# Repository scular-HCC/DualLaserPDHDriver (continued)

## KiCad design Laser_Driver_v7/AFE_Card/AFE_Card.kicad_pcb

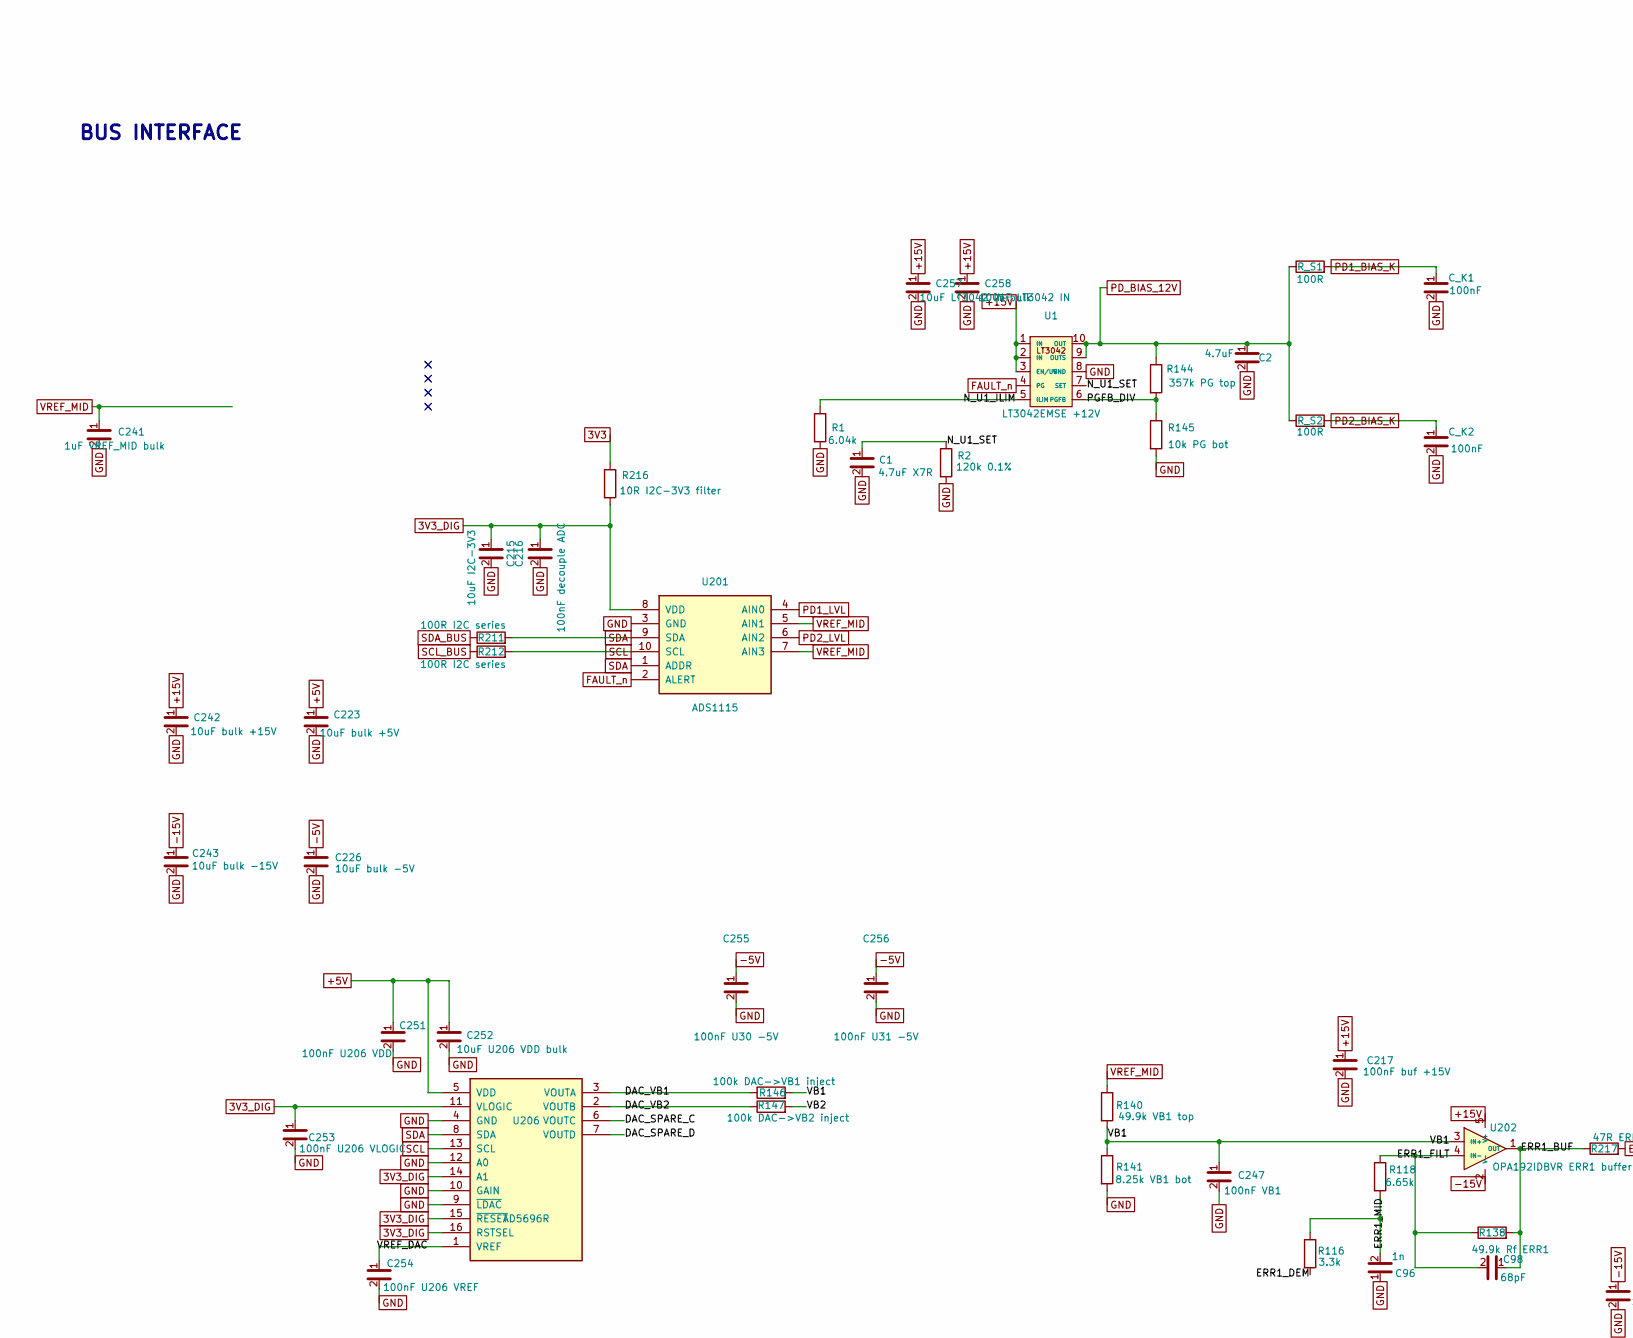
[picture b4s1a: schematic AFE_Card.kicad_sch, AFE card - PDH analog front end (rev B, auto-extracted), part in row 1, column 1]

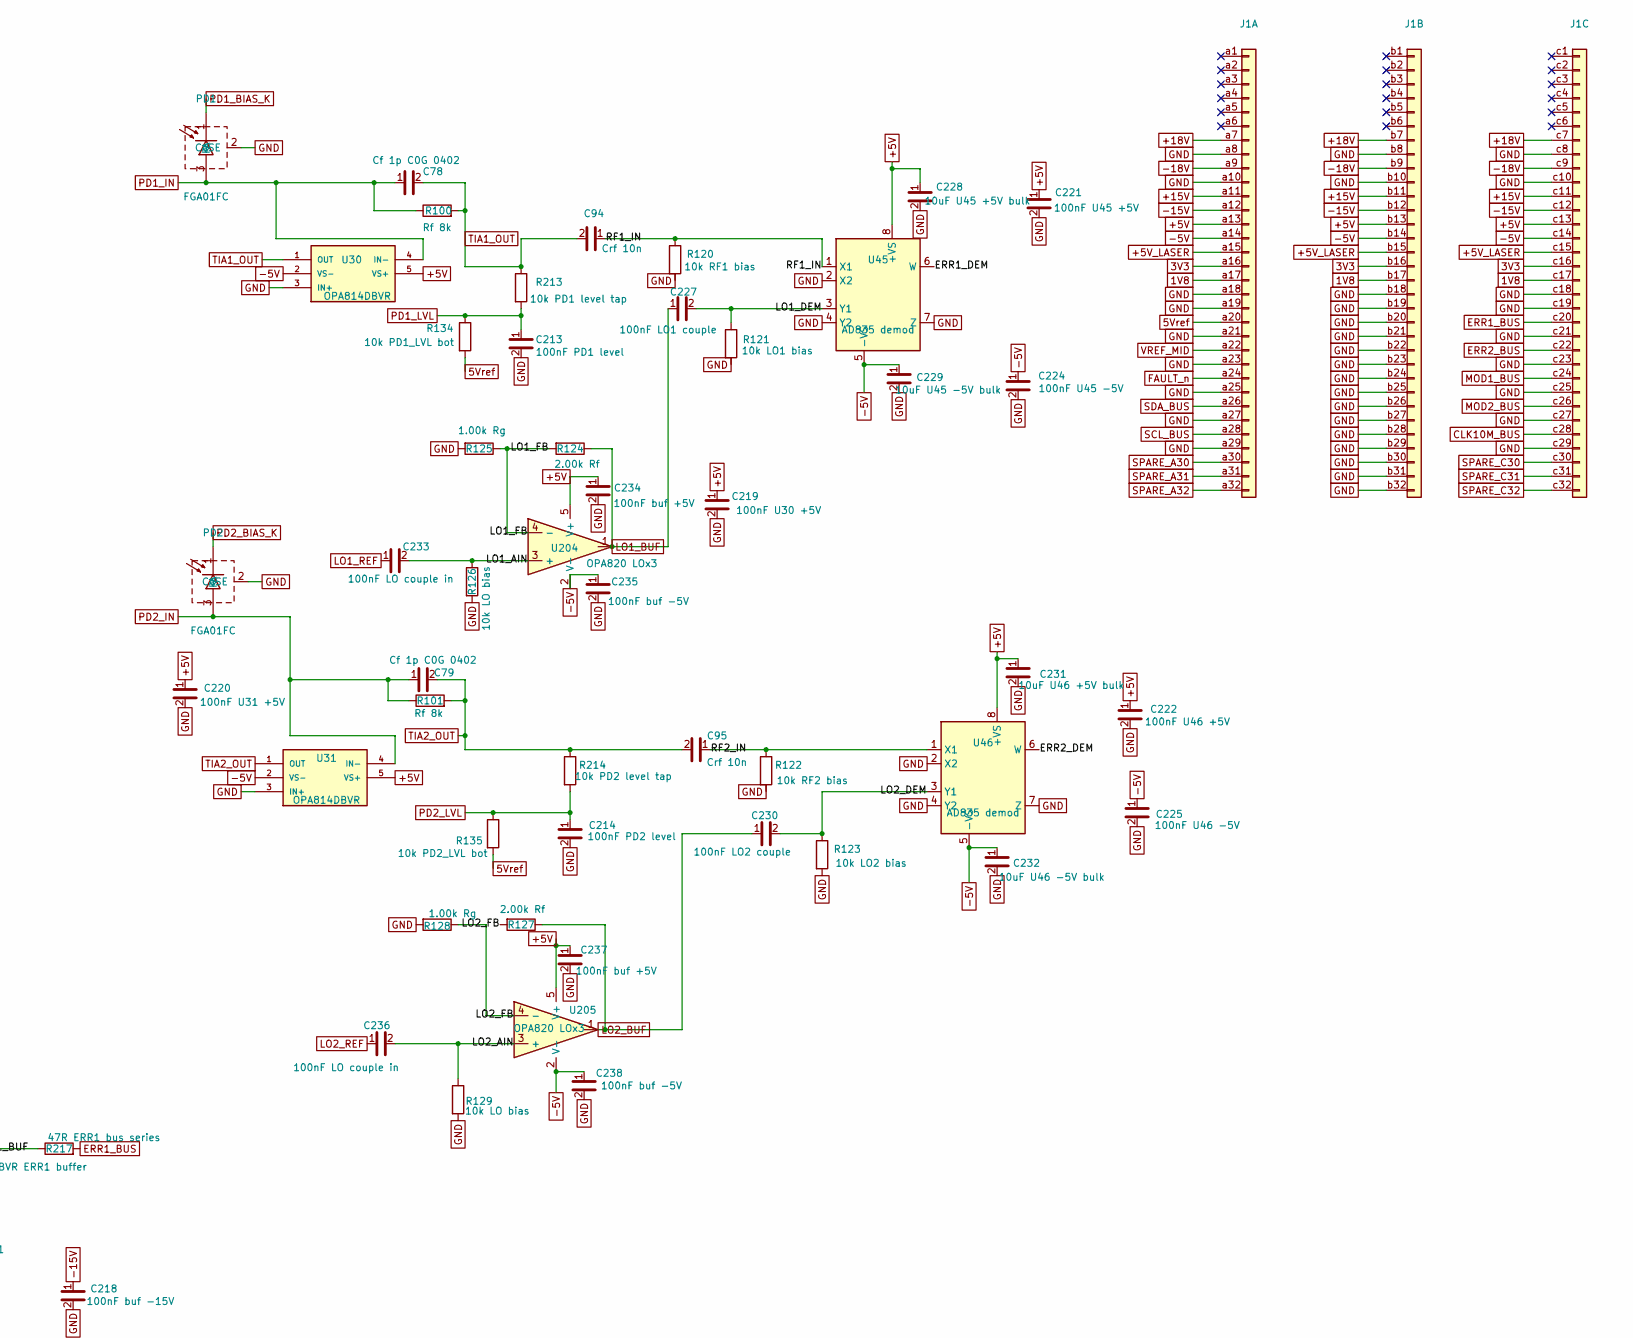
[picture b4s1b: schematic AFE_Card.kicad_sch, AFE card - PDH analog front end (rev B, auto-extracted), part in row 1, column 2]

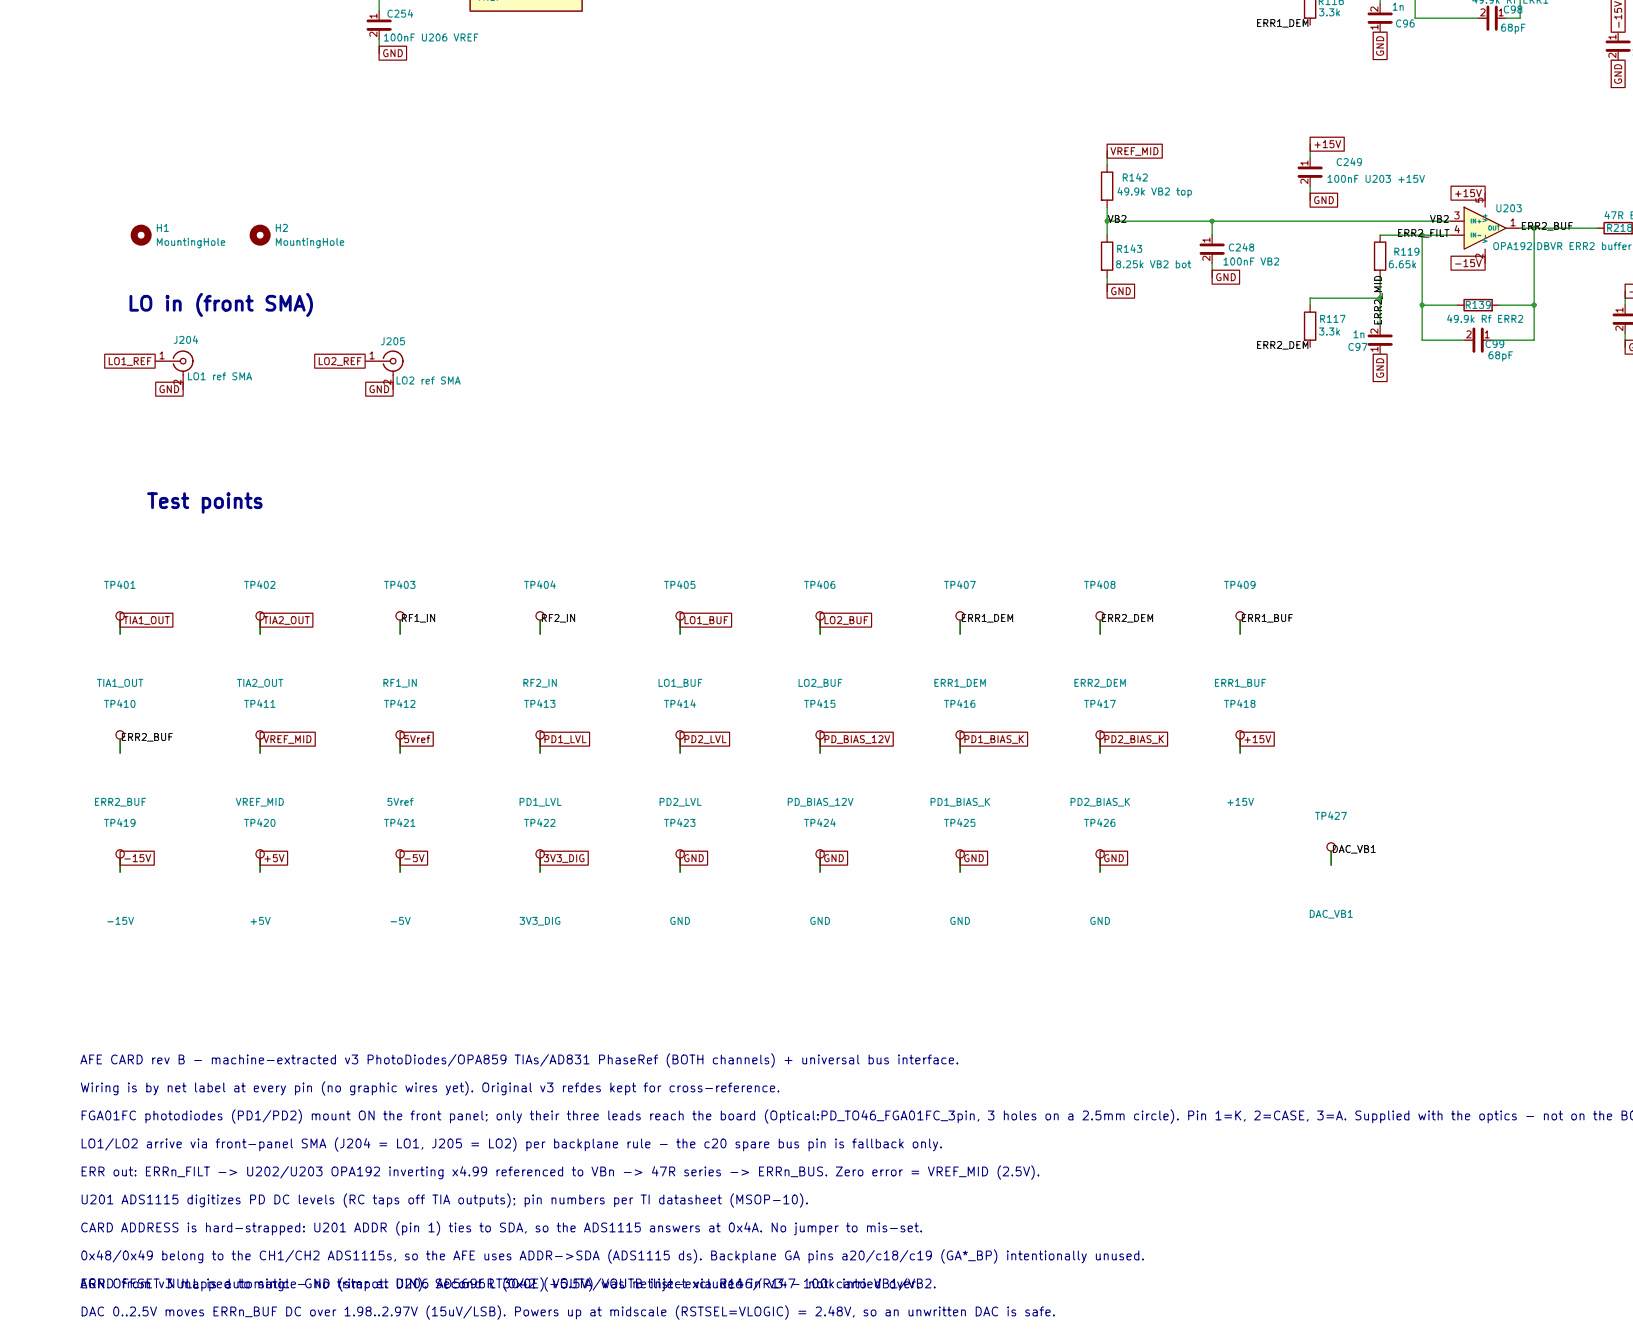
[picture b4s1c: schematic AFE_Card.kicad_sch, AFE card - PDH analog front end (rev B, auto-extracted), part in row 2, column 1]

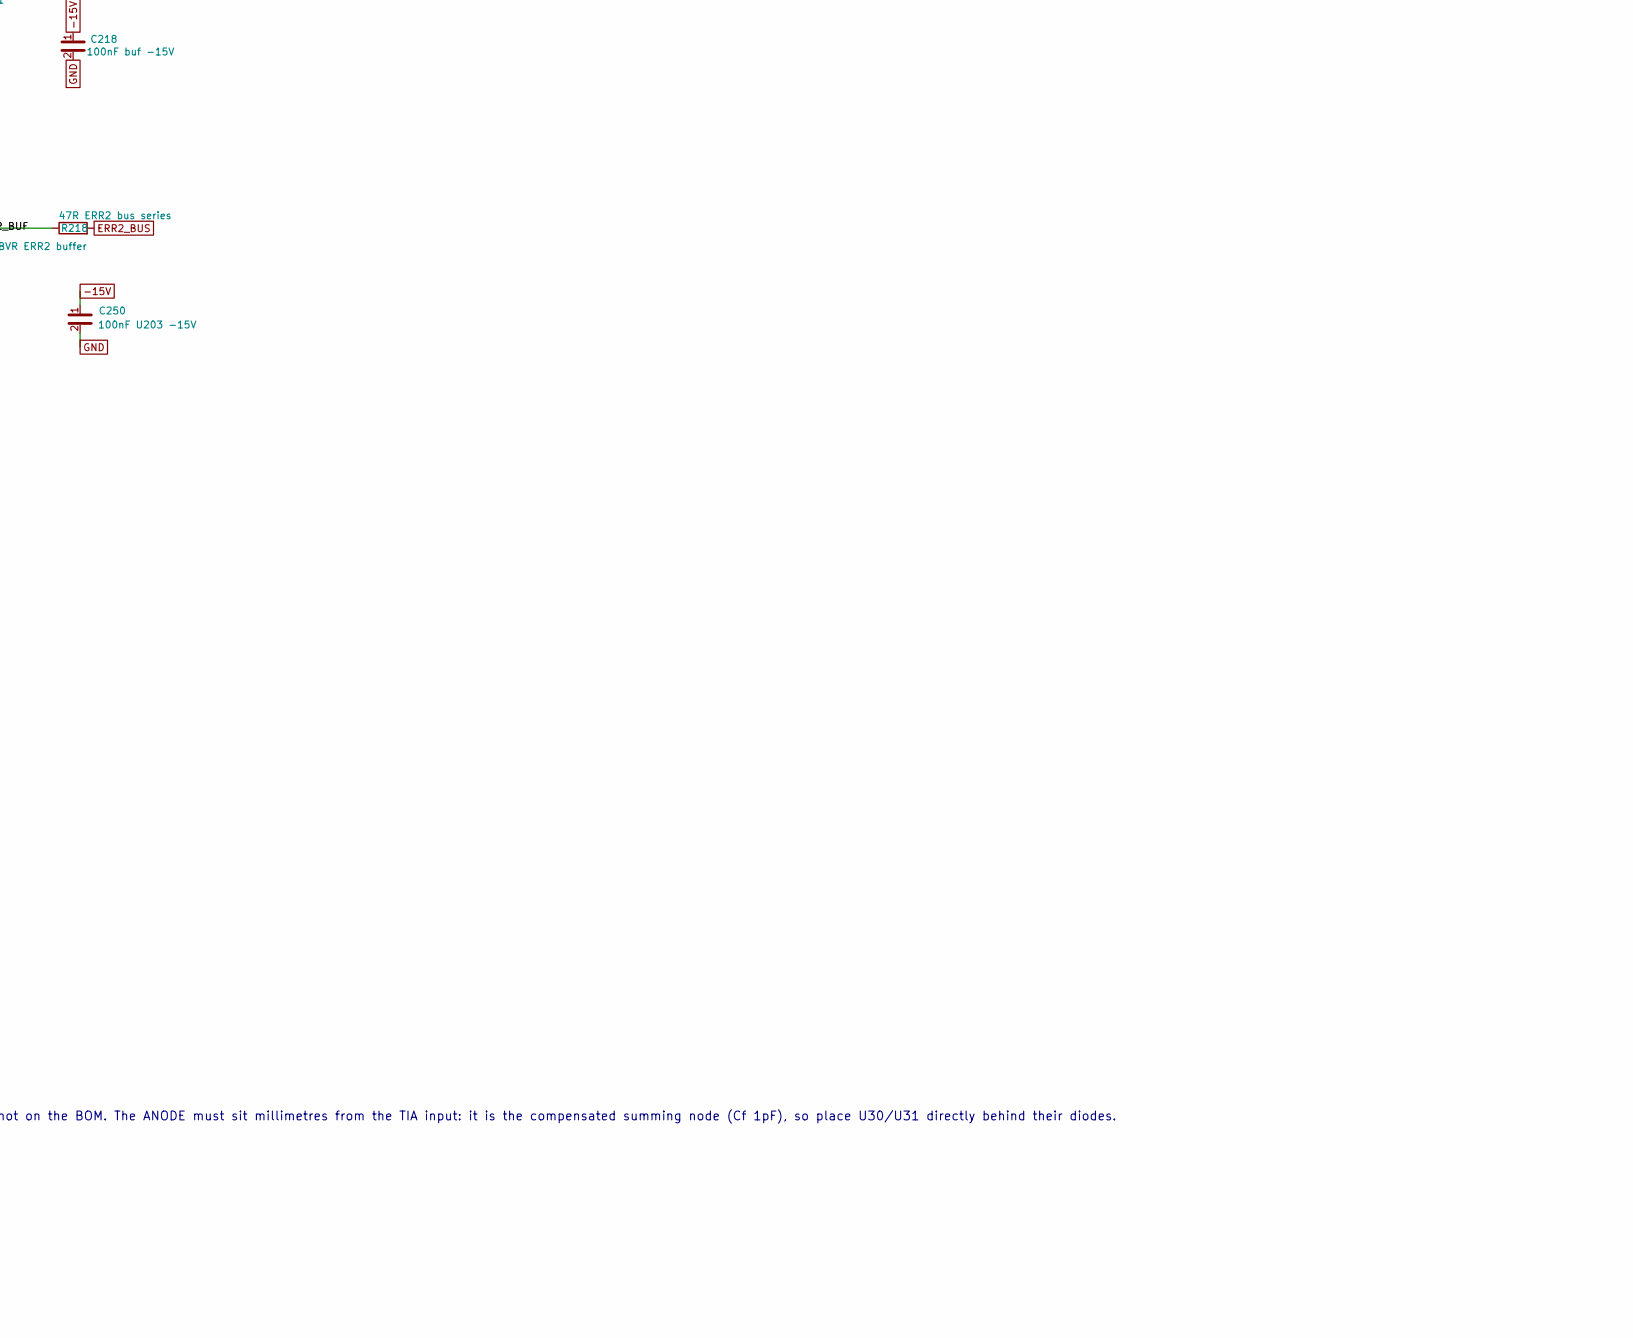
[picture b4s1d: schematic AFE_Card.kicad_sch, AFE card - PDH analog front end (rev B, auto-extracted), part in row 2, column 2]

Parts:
C1: 4.7uF X7R; C_0805_2012Metric_Pad1.18x1.45mm_HandSolder
C2: 4.7uF; C_0805_2012Metric_Pad1.18x1.45mm_HandSolder
C78, C79: Cf 1p C0G 0402; C_0402_1005Metric_Pad0.74x0.62mm_HandSolder
C94, C95: Crf 10n; C_0805_2012Metric_Pad1.18x1.45mm_HandSolder
C96, C97: 1n; C_0805_2012Metric_Pad1.18x1.45mm_HandSolder
C98, C99: 68pF; C_0805_2012Metric_Pad1.18x1.45mm_HandSolder
C213: 100nF PD1 level; C_0805_2012Metric_Pad1.18x1.45mm_HandSolder
C214: 100nF PD2 level; C_0805_2012Metric_Pad1.18x1.45mm_HandSolder
C215: 10uF I2C-3V3; C_0805_2012Metric_Pad1.18x1.45mm_HandSolder
C216: 100nF decouple ADC; C_0805_2012Metric_Pad1.18x1.45mm_HandSolder
C217: 100nF buf +15V; C_0805_2012Metric_Pad1.18x1.45mm_HandSolder
C218: 100nF buf -15V; C_0805_2012Metric_Pad1.18x1.45mm_HandSolder
C219: 100nF U30 +5V; C_0805_2012Metric_Pad1.18x1.45mm_HandSolder
C220: 100nF U31 +5V; C_0805_2012Metric_Pad1.18x1.45mm_HandSolder
C221: 100nF U45 +5V; C_0805_2012Metric_Pad1.18x1.45mm_HandSolder
C222: 100nF U46 +5V; C_0805_2012Metric_Pad1.18x1.45mm_HandSolder
C223: 10uF bulk +5V; C_0805_2012Metric_Pad1.18x1.45mm_HandSolder
C224: 100nF U45 -5V; C_0805_2012Metric_Pad1.18x1.45mm_HandSolder
C225: 100nF U46 -5V; C_0805_2012Metric_Pad1.18x1.45mm_HandSolder
C226: 10uF bulk -5V; C_0805_2012Metric_Pad1.18x1.45mm_HandSolder
C227: 100nF LO1 couple; C_0805_2012Metric_Pad1.18x1.45mm_HandSolder
C228: 10uF U45 +5V bulk; C_0805_2012Metric_Pad1.18x1.45mm_HandSolder
C229: 10uF U45 -5V bulk; C_0805_2012Metric_Pad1.18x1.45mm_HandSolder
C230: 100nF LO2 couple; C_0805_2012Metric_Pad1.18x1.45mm_HandSolder
C231: 10uF U46 +5V bulk; C_0805_2012Metric_Pad1.18x1.45mm_HandSolder
C232: 10uF U46 -5V bulk; C_0805_2012Metric_Pad1.18x1.45mm_HandSolder
C233, C236: 100nF LO couple in; C_0805_2012Metric_Pad1.18x1.45mm_HandSolder
C234, C237: 100nF buf +5V; C_0805_2012Metric_Pad1.18x1.45mm_HandSolder
C235, C238: 100nF buf -5V; C_0805_2012Metric_Pad1.18x1.45mm_HandSolder
C241: 1uF VREF_MID bulk; C_0805_2012Metric_Pad1.18x1.45mm_HandSolder
C242: 10uF bulk +15V; C_0805_2012Metric_Pad1.18x1.45mm_HandSolder
C243: 10uF bulk -15V; C_0805_2012Metric_Pad1.18x1.45mm_HandSolder
C247: 100nF VB1; C_0805_2012Metric_Pad1.18x1.45mm_HandSolder
C248: 100nF VB2; C_0805_2012Metric_Pad1.18x1.45mm_HandSolder
C249: 100nF U203 +15V; C_0805_2012Metric_Pad1.18x1.45mm_HandSolder
C250: 100nF U203 -15V; C_0805_2012Metric_Pad1.18x1.45mm_HandSolder
C251: 100nF U206 VDD; C_0805_2012Metric_Pad1.18x1.45mm_HandSolder
C252: 10uF U206 VDD bulk; C_0805_2012Metric_Pad1.18x1.45mm_HandSolder
C253: 100nF U206 VLOGIC; C_0805_2012Metric_Pad1.18x1.45mm_HandSolder
C254: 100nF U206 VREF; C_0805_2012Metric_Pad1.18x1.45mm_HandSolder
C255: 100nF U30 -5V; C_0805_2012Metric_Pad1.18x1.45mm_HandSolder
C256: 100nF U31 -5V; C_0805_2012Metric_Pad1.18x1.45mm_HandSolder
C257: 10uF LT3042 IN bulk; C_0805_2012Metric_Pad1.18x1.45mm_HandSolder
C258: 100nF LT3042 IN; C_0805_2012Metric_Pad1.18x1.45mm_HandSolder
C_K1, C_K2: 100nF; C_0805_2012Metric_Pad1.18x1.45mm_HandSolder
H1, H2: MountingHole; MountingHole_2.7mm
J1: DIN41612_03x32_C_Split; DIN41612_C_3x32_Male_Horizontal_THT
J204: LO1 ref SMA; SMA_Amphenol_132203-12_Horizontal
J205: LO2 ref SMA; SMA_Amphenol_132203-12_Horizontal
PD1, PD2: FGA01FC; PD_FGA01FC_EdgeBracket
R1: 6.04k; R_0805_2012Metric_Pad1.20x1.40mm_HandSolder
R2: 120k 0.1%; R_0805_2012Metric_Pad1.20x1.40mm_HandSolder
R100, R101: Rf 8k; R_0805_2012Metric_Pad1.20x1.40mm_HandSolder
R116, R117: 3.3k; R_0805_2012Metric_Pad1.20x1.40mm_HandSolder
R118, R119: 6.65k; R_0805_2012Metric_Pad1.20x1.40mm_HandSolder
R120: 10k RF1 bias; R_0805_2012Metric_Pad1.20x1.40mm_HandSolder
R121: 10k LO1 bias; R_0805_2012Metric_Pad1.20x1.40mm_HandSolder
R122: 10k RF2 bias; R_0805_2012Metric_Pad1.20x1.40mm_HandSolder
R123: 10k LO2 bias; R_0805_2012Metric_Pad1.20x1.40mm_HandSolder
R124, R127: 2.00k Rf; R_0805_2012Metric_Pad1.20x1.40mm_HandSolder
R125, R128: 1.00k Rg; R_0805_2012Metric_Pad1.20x1.40mm_HandSolder
R126, R129: 10k LO bias; R_0805_2012Metric_Pad1.20x1.40mm_HandSolder
R134: 10k PD1_LVL bot; R_0805_2012Metric_Pad1.20x1.40mm_HandSolder
R135: 10k PD2_LVL bot; R_0805_2012Metric_Pad1.20x1.40mm_HandSolder
R138: 49.9k Rf ERR1; R_0805_2012Metric_Pad1.20x1.40mm_HandSolder
R139: 49.9k Rf ERR2; R_0805_2012Metric_Pad1.20x1.40mm_HandSolder
R140: 49.9k VB1 top; R_0805_2012Metric_Pad1.20x1.40mm_HandSolder
R141: 8.25k VB1 bot; R_0805_2012Metric_Pad1.20x1.40mm_HandSolder
R142: 49.9k VB2 top; R_0805_2012Metric_Pad1.20x1.40mm_HandSolder
R143: 8.25k VB2 bot; R_0805_2012Metric_Pad1.20x1.40mm_HandSolder
R144: 357k PG top; R_0805_2012Metric_Pad1.20x1.40mm_HandSolder
R145: 10k PG bot; R_0805_2012Metric_Pad1.20x1.40mm_HandSolder
R146: 100k DAC->VB1 inject; R_0805_2012Metric_Pad1.20x1.40mm_HandSolder
R147: 100k DAC->VB2 inject; R_0805_2012Metric_Pad1.20x1.40mm_HandSolder
R211, R212: 100R I2C series; R_0805_2012Metric_Pad1.20x1.40mm_HandSolder
R213: 10k PD1 level tap; R_0805_2012Metric_Pad1.20x1.40mm_HandSolder
R214: 10k PD2 level tap; R_0805_2012Metric_Pad1.20x1.40mm_HandSolder
R216: 10R I2C-3V3 filter; R_0805_2012Metric_Pad1.20x1.40mm_HandSolder
R217: 47R ERR1 bus series; R_0805_2012Metric_Pad1.20x1.40mm_HandSolder
R218: 47R ERR2 bus series; R_0805_2012Metric_Pad1.20x1.40mm_HandSolder
R_S1, R_S2: 100R; R_0805_2012Metric_Pad1.20x1.40mm_HandSolder
TP401: TIA1_OUT; TestPoint_Pad_D1.0mm
TP402: TIA2_OUT; TestPoint_Pad_D1.0mm
TP403: RF1_IN; TestPoint_Pad_D1.0mm
TP404: RF2_IN; TestPoint_Pad_D1.0mm
TP405: LO1_BUF; TestPoint_Pad_D1.0mm
TP406: LO2_BUF; TestPoint_Pad_D1.0mm
TP407: ERR1_DEM; TestPoint_Pad_D1.0mm
TP408: ERR2_DEM; TestPoint_Pad_D1.0mm
TP409: ERR1_BUF; TestPoint_Pad_D1.0mm
TP410: ERR2_BUF; TestPoint_Pad_D1.0mm
TP411: VREF_MID; TestPoint_Pad_D1.0mm
TP412: 5Vref; TestPoint_Pad_D1.0mm
TP413: PD1_LVL; TestPoint_Pad_D1.0mm
TP414: PD2_LVL; TestPoint_Pad_D1.0mm
TP415: PD_BIAS_12V; TestPoint_Pad_D1.0mm
TP416: PD1_BIAS_K; TestPoint_Pad_D1.0mm
TP417: PD2_BIAS_K; TestPoint_Pad_D1.0mm
TP418: +15V; TestPoint_Pad_D1.0mm
TP419: -15V; TestPoint_Pad_D1.0mm
TP420: +5V; TestPoint_Pad_D1.0mm
TP421: -5V; TestPoint_Pad_D1.0mm
TP422: 3V3_DIG; TestPoint_Pad_D1.0mm
TP423, TP424, TP425, TP426: GND; TestPoint_THTPad_D1.5mm_Drill0.7mm
TP427: DAC_VB1; TestPoint_Pad_D1.0mm
U1: LT3042EMSE +12V; MSOP-10-1EP_3x3mm_P0.5mm_EP1.68x1.88mm
U30, U31: OPA814DBVR; MOUSER_PART_NUMBER 595-OPA814DBVR
U45, U46: AD835 demod; SOIC-8_3.9x4.9mm_P1.27mm
U201: ADS1115; MSOP-10_3x3mm_P0.5mm
U202: OPA192IDBVR ERR1 buffer; SOT-23-5
U203: OPA192IDBVR ERR2 buffer; SOT-23-5
U204, U205: OPA820 LOx3; SOT-23-5
U206: AD5696R; TSSOP-16_4.4x5mm_P0.65mm

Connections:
1V8: J1.a17, J1.b17, J1.c17
3V3: J1.a16, J1.b16, J1.c16, R216.1
3V3_DIG: C215.1, C216.1, C253.1, R216.2, TP422.1 (1_1), U201.8 (VDD), U206.11 (VLOGIC), U206.14 (A1), U206.15 (~RESET), U206.16 (RSTSEL)
5Vref: J1.a20, R134.2, R135.2, TP412.1 (1_1)
+5V: C219.1, C220.1, C221.1, C222.1, C223.1, C228.1, C231.1, C234.1, C237.1, C251.1, C252.1, J1.a13, J1.b13, J1.c13, TP420.1 (1_1), U30.5 (VS+), U31.5 (VS+), U45.8 (+VS), U46.8 (+VS), U204.5 (V+), U205.5 (V+), U206.5 (VDD)
+5V_LASER: J1.a15, J1.b15, J1.c15
+15V: C217.1, C242.1, C249.1, C257.1, C258.1, J1.a11, J1.b11, J1.c11, TP418.1 (1_1), U1.1 (IN), U1.2 (IN), U1.3 (EN/UV), U202.5 (V+), U203.5 (V+)
+18V: J1.a7, J1.b7, J1.c7
-5V: C224.1, C225.1, C226.1, C229.1, C232.1, C235.1, C238.1, C255.1, C256.1, J1.a14, J1.b14, J1.c14, TP421.1 (1_1), U30.2 (VS-), U31.2 (VS-), U45.5 (-VS), U46.5 (-VS), U204.2 (V-), U205.2 (V-)
-15V: C218.1, C243.1, C250.1, J1.a12, J1.b12, J1.c12, TP419.1 (1_1), U202.2 (V-), U203.2 (V-)
-18V: J1.a9, J1.b9, J1.c9
/DAC_SPARE_C: U206.6 (VOUTC)
/DAC_SPARE_D: U206.7 (VOUTD)
/DAC_VB1: R146.1, TP427.1 (1_1), U206.3 (VOUTA)
/DAC_VB2: R147.1, U206.2 (VOUTB)
/ERR1_BUF: C98.1, R138.2, R217.1, TP409.1 (1_1), U202.1 (OUT)
/ERR1_DEM: R116.2, TP407.1 (1_1), U45.6 (W)
/ERR1_FILT: C98.2, R118.1, R138.1, U202.4 (IN-)
/ERR1_MID: C96.2, R116.1, R118.2
/ERR2_BUF: C99.1, R139.2, R218.1, TP410.1 (1_1), U203.1 (OUT)
/ERR2_DEM: R117.2, TP408.1 (1_1), U46.6 (W)
/ERR2_FILT: C99.2, R119.1, R139.1, U203.4 (IN-)
/ERR2_MID: C97.2, R117.1, R119.2
/LO1_AIN: C233.2, R126.1, U204.3 (+)
/LO1_DEM: C227.2, R121.1, U45.3 (Y1)
/LO1_FB: R124.2, R125.1, U204.4 (-)
/LO2_AIN: C236.2, R129.1, U205.3 (+)
/LO2_DEM: C230.2, R123.1, U46.3 (Y1)
/LO2_FB: R127.2, R128.1, U205.4 (-)
/N_U1_ILIM: R1.1, U1.5 (ILIM)
/N_U1_SET: C1.1, R2.1, U1.7 (SET)
/PGFB_DIV: R144.2, R145.1, U1.6 (PGFB)
/RF1_IN: C94.1, R120.1, TP403.1 (1_1), U45.1 (X1)
/RF2_IN: C95.1, R122.1, TP404.1 (1_1), U46.1 (X1)
/VB1: C247.1, R140.2, R141.1, R146.2, U202.3 (IN+)
/VB2: C248.1, R142.2, R143.1, R147.2, U203.3 (IN+)
/VREF_DAC: C254.1, U206.1 (VREF)
CLK10M_BUS: J1.c28
ERR1_BUS: J1.c20, R217.2
ERR2_BUS: J1.c22, R218.2
FAULT_n: J1.a24, U1.4 (PG), U201.2 (ALERT)
GND: C1.2, C2.2, C96.1, C97.1, C213.2, C214.2, C215.2, C216.2, C217.2, C218.2, C219.2, C220.2, C221.2, C222.2, C223.2, C224.2, C225.2, C226.2, C228.2, C229.2, C231.2, C232.2, C234.2, C235.2, C237.2, C238.2, C241.2, C242.2, C243.2, C247.2, C248.2, C249.2, C250.2, C251.2, C252.2, C253.2, C254.2, C255.2, C256.2, C257.2, C258.2, C_K1.2, C_K2.2, J1.a8, J1.a10, J1.a18, J1.a19, J1.a21, J1.a23, J1.a25, J1.a27, J1.a29, J1.b8, J1.b10, J1.b18, J1.b19, J1.b20, J1.b21, J1.b22, J1.b23, J1.b24, J1.b25, J1.b26, J1.b27, J1.b28, J1.b29, J1.b30, J1.b31, J1.b32, J1.c8, J1.c10, J1.c18, J1.c19, J1.c21, J1.c23, J1.c25, J1.c27, J1.c29, J204.2 (Ext), J205.2 (Ext), PD1.2 (CASE), PD2.2 (CASE), R1.2, R2.2, R120.2, R121.2, R122.2, R123.2, R125.2, R126.2, R128.2, R129.2, R141.2, R143.2, R145.2, TP423.1 (1_1), TP424.1 (1_1), TP425.1 (1_1), TP426.1 (1_1), U1.8 (GND), U1.11 (Pad), U30.3 (IN+), U31.3 (IN+), U45.2 (X2), U45.4 (Y2), U45.7 (Z), U46.2 (X2), U46.4 (Y2), U46.7 (Z), U201.3 (GND), U206.4 (GND), U206.9 (~LDAC), U206.10 (GAIN), U206.12 (A0)
LO1_BUF: C227.1, R124.1, TP405.1 (1_1), U204.1
LO1_REF: C233.1, J204.1 (In)
LO2_BUF: C230.1, R127.1, TP406.1 (1_1), U205.1
LO2_REF: C236.1, J205.1 (In)
MOD1_BUS: J1.c24
MOD2_BUS: J1.c26
PD1_BIAS_K: C_K1.1, PD1.1 (K), R_S1.2, TP416.1 (1_1)
PD1_IN: C78.1, PD1.3 (A), R100.1, U30.4 (IN-)
PD1_LVL: C213.1, R134.1, R213.2, TP413.1 (1_1), U201.4 (AIN0)
PD2_BIAS_K: C_K2.1, PD2.1 (K), R_S2.2, TP417.1 (1_1)
PD2_IN: C79.1, PD2.3 (A), R101.1, U31.4 (IN-)
PD2_LVL: C214.1, R135.1, R214.2, TP414.1 (1_1), U201.6 (AIN2)
PD_BIAS_12V: C2.1, R144.1, R_S1.1, R_S2.1, TP415.1 (1_1), U1.9 (OUTS), U1.10 (OUT)
SCL: R212.2, U201.10 (SCL), U206.13 (SCL)
SCL_BUS: J1.a28, R212.1
SDA: R211.2, U201.1 (ADDR), U201.9 (SDA), U206.8 (SDA)
SDA_BUS: J1.a26, R211.1
SPARE_A30: J1.a30
SPARE_A31: J1.a31
SPARE_A32: J1.a32
SPARE_C30: J1.c30
SPARE_C31: J1.c31
SPARE_C32: J1.c32
TIA1_OUT: C78.2, C94.2, R100.2, R213.1, TP401.1 (1_1), U30.1 (OUT)
TIA2_OUT: C79.2, C95.2, R101.2, R214.1, TP402.1 (1_1), U31.1 (OUT)
VREF_MID: C241.1, J1.a22, R140.1, R142.1, TP411.1 (1_1), U201.5 (AIN1), U201.7 (AIN3)

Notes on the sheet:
AFE CARD rev B - machine-extracted v3 PhotoDiodes/OPA859 TIAs/AD831 PhaseRef (BOTH channels) + universal bus interface.
U201 ADS1115 digitizes PD DC levels (RC taps off TIA outputs); pin numbers per TI datasheet (MSOP-10).
LO in (front SMA)
CARD ADDRESS is hard-strapped: U201 ADDR (pin 1) ties to SDA, so the ADS1115 answers at 0x4A. No jumper to mis-set.
LO1/LO2 arrive via front-panel SMA (J204 = LO1, J205 = LO2) per backplane rule - the c20 spare bus pin is fallback only.
Test points
BUS INTERFACE
Wiring is by net label at every pin (no graphic wires yet). Original v3 refdes kept for cross-reference.
DAC 0..2.5V moves ERRn_BUF DC over 1.98..2.97V (15uV/LSB). Powers up at midscale (RSTSEL=VLOGIC) = 2.48V, so an unwritten DAC is safe.
AGND from v3 mapped to single GND (star at DIN). Second LT3042 (+5.5V) was netlist-excluded in v3 - not carried over.
FGA01FC photodiodes (PD1/PD2) mount ON the front panel; only their three leads reach the board (Optical:PD_TO46_FGA01FC_3pin, 3 holes on a 2.5mm circle). Pin 1=K, 2=CASE, 3=A. Supplied with the optics - not on the BOM. The ANODE must sit millimetres from the TIA input: it is the compensated summing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
ERR out: ERRn_FILT -> U202/U203 OPA192 inverting x4.99 referenced to VBn -> 47R series -> ERRn_BUS. Zero error = VREF_MID (2.5V).
ERR OFFSET NULL is automatic - no trimpot. U206 AD5696R (0x0E) VOUTA/VOUTB inject via R146/R147 100k into VB1/VB2.
0x48/0x49 belong to the CH1/CH2 ADS1115s, so the AFE uses ADDR->SDA (ADS1115 ds). Backplane GA pins a20/c18/c19 (GA*_BP) intentionally unused.

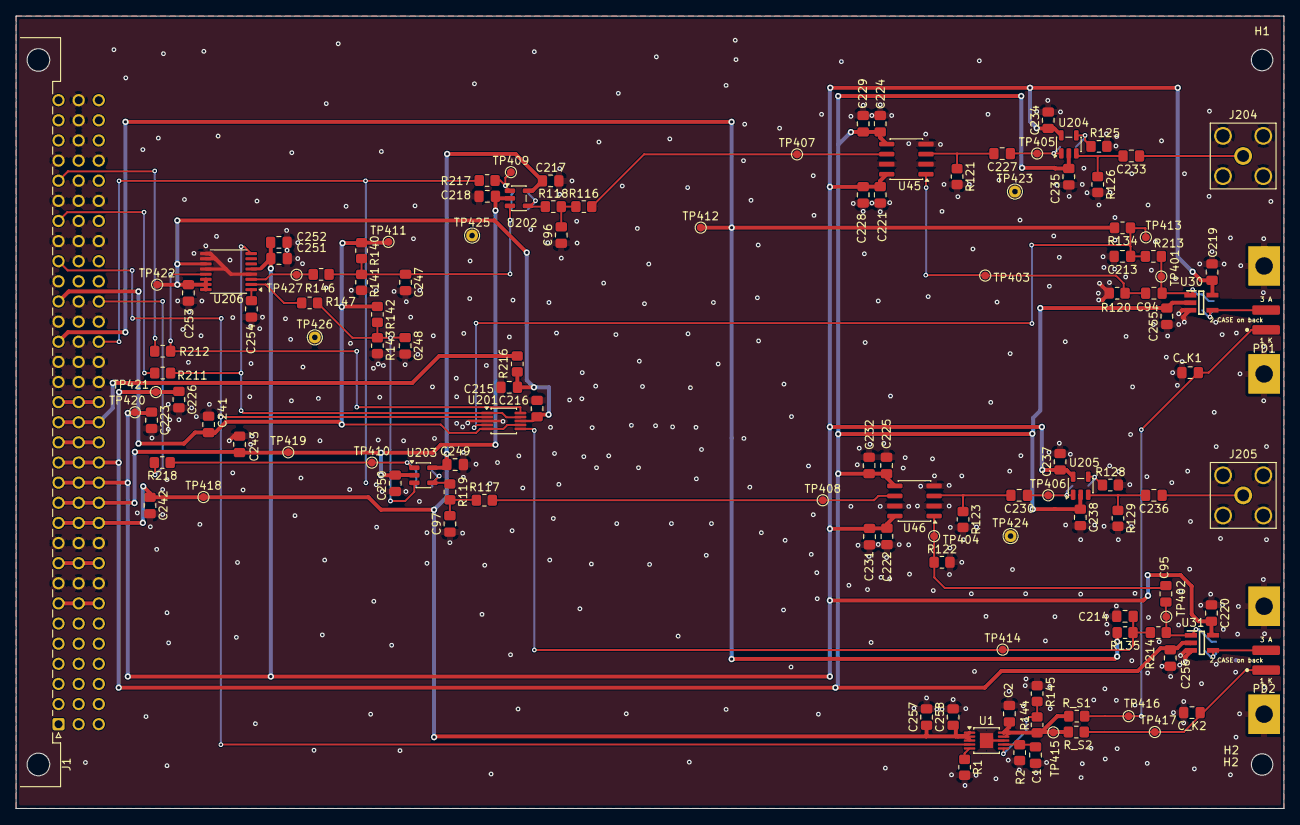
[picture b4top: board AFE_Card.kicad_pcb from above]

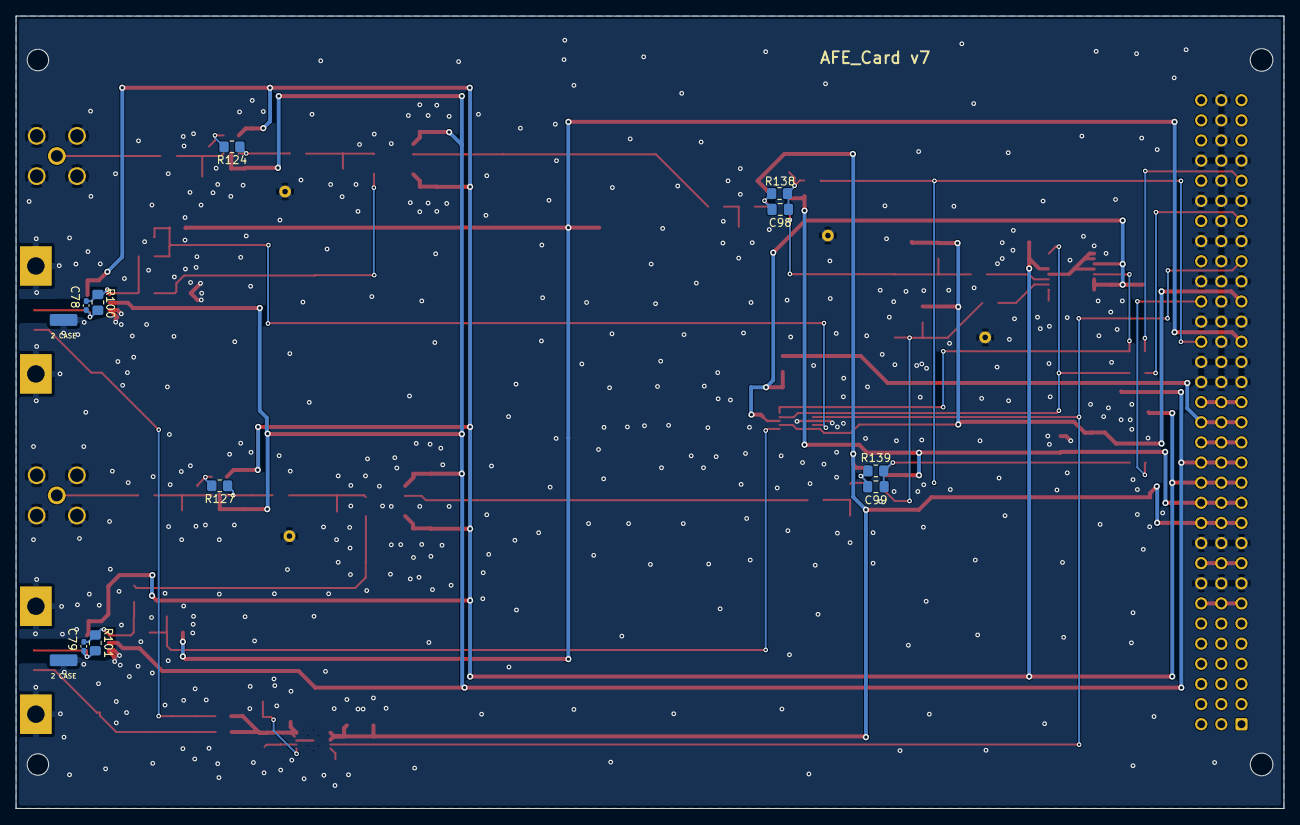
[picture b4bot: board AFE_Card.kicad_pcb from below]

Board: 2 copper layers, 160.0 x 100.0 mm, 137 parts (10 on the bottom side), 57 nets.

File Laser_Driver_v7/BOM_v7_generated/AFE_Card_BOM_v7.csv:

Quantity,Manufacturer Part Number,Manufacturer,Customer Reference,Value,Footprint
2,C0805C475K3RACTU,Kemet,"C1,C2",4.7uF X7R,C_0805_2012Metric_Pad1.18x1.45mm_HandSolder
2,C0402C109C5GACTU,KEMET,"C78,C79",Cf 1p C0G 0402,C_0402_1005Metric_Pad0.74x0.62mm_HandSolder
2,CL21B103KBANNNC,Samsung Electro-Mechanics,"C94,C95",Crf 10n,C_0805_2012Metric_Pad1.18x1.45mm_HandSolder
2,CL21B102KBANNNC,Samsung,"C96,C97",1n,C_0805_2012Metric_Pad1.18x1.45mm_HandSolder
2,C0805C680J5GACTU,Kemet,"C98,C99",68pF,C_0805_2012Metric_Pad1.18x1.45mm_HandSolder
31,CL21B104KBCNNNC,Samsung,"C213,C214,C216,C217,C218,C219,C220,C221,C222,C224,C225,C227,C230,C233,C234,C235,C236,C237,C238,C247,C248,C249,C250,C251,C253,C254,C255,C256,C258,C_K1,C_K2",100nF PD1 level,C_0805_2012Metric_Pad1.18x1.45mm_HandSolder
11,C0805C106K3PACTU,Kemet,"C215,C223,C226,C228,C229,C231,C232,C242,C243,C252,C257",10uF I2C-3V3,C_0805_2012Metric_Pad1.18x1.45mm_HandSolder
1,C0805C105K5RACTU,Kemet,C241,1uF VREF_MID bulk,C_0805_2012Metric_Pad1.18x1.45mm_HandSolder
1,09031966921,HARTING,J1,DIN41612_03x32_C_Split,DIN41612_C_3x32_Male_Horizontal_THT
2,132203-12,Amphenol RF,"J204,J205",LO1 ref SMA,SMA_Amphenol_132203-12_Horizontal
2,FGA01FC,Thorlabs,"PD1,PD2",FGA01FC,PD_FGA01FC_EdgeBracket
1,ERA-6AEB6041V,Panasonic,R1,6.04k,R_0805_2012Metric_Pad1.20x1.40mm_HandSolder
1,ERA-6AEB124V,Panasonic,R2,120k 0.1%,R_0805_2012Metric_Pad1.20x1.40mm_HandSolder
2,ERA-6AEB8061V,Panasonic,"R100,R101",Rf 8k,R_0805_2012Metric_Pad1.20x1.40mm_HandSolder
2,RC0805FR-073K3L,Yageo,"R116,R117",3.3k,R_0805_2012Metric_Pad1.20x1.40mm_HandSolder
2,ERA-6AEB6651V,Panasonic,"R118,R119",6.65k,R_0805_2012Metric_Pad1.20x1.40mm_HandSolder
11,RC0805FR-0710KL,Yageo,"R120,R121,R122,R123,R126,R129,R134,R135,R145,R213,R214",10k RF1 bias,R_0805_2012Metric_Pad1.20x1.40mm_HandSolder
2,ERA-6AEB202V,Panasonic,"R124,R127",2.00k Rf,R_0805_2012Metric_Pad1.20x1.40mm_HandSolder
2,CRCW08051K00FKEA,Vishay Dale,"R125,R128",1.00k Rg,R_0805_2012Metric_Pad1.20x1.40mm_HandSolder
4,ERA-6AEB4992V,Panasonic,"R138,R139,R140,R142",49.9k Rf ERR1,R_0805_2012Metric_Pad1.20x1.40mm_HandSolder
2,ERA-6AEB8251V,Panasonic,"R141,R143",8.25k VB1 bot,R_0805_2012Metric_Pad1.20x1.40mm_HandSolder
1,ERJ-6ENF3573V,Panasonic,R144,357k PG top,R_0805_2012Metric_Pad1.20x1.40mm_HandSolder
2,ERA-6AEB104V,Panasonic,"R146,R147",100k DAC->VB1 inject,R_0805_2012Metric_Pad1.20x1.40mm_HandSolder
4,RC0805FR-07100RL,Yageo,"R211,R212,R_S1,R_S2",100R I2C series,R_0805_2012Metric_Pad1.20x1.40mm_HandSolder
1,RC0805FR-0710RL,Yageo,R216,10R I2C-3V3 filter,R_0805_2012Metric_Pad1.20x1.40mm_HandSolder
2,RC0805FR-0747RL,Yageo,"R217,R218",47R ERR1 bus series,R_0805_2012Metric_Pad1.20x1.40mm_HandSolder
1,LT3042EMSE#PBF,Analog Devices,U1,LT3042EMSE +12V,MSOP-10-1EP_3x3mm_P0.5mm_EP2.2x3.1mm_Mask1.83x1.89mm_ThermalVias
2,OPA814DBVR,Texas Instruments,"U30,U31",OPA814DBVR,OPA814DBVR
2,AD835ARZ,Analog Devices,"U45,U46",AD835 demod,SOIC-8_3.9x4.9mm_P1.27mm
1,ADS1115IDGSR,Texas Instruments,U201,ADS1115,MSOP-10_3x3mm_P0.5mm
2,OPA192IDBVR,Texas Instruments,"U202,U203",OPA192IDBVR ERR1 buffer,SOT-23-5
2,OPA820IDBVR,Texas Instruments,"U204,U205",OPA820 LOx3,SOT-23-5
1,AD5696RARUZ,Analog Devices,U206,AD5696R,TSSOP-16_4.4x5mm_P0.65mm
